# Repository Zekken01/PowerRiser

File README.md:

# PowerRiser – Lenovo Tiny 5 PCIe x8 + M.2 NVMe Riser (fork)

A passive riser for Lenovo Tiny 5 series PCs. It breaks the proprietary Lenovo riser connector out to an x8 PCIe slot and adds a 4-lane M.2 NVMe slot (2230/2242).

This is a modified fork of [nandfarm/PowerRiser](https://github.com/nandfarm/PowerRiser), which was inspired by [TinyRiser](https://github.com/a-little-wifi/Tinyriser) by WifiCable. See [Changes from upstream](#changes-from-upstream).

> ⚠ The changes in this fork have not been tested on hardware yet.

## Compatibility

Lenovo Tiny 5 series (8th/9th gen):

- ThinkCentre M720q
- ThinkCentre M920q
- ThinkCentre M920x
- ThinkStation P330 Tiny

It replaces the Lenovo risers with FRU codes 01AJ940, 01AJ902 and 01AJ929, and adds the M.2 slot. The back silkscreen also lists NEC Mate MC-3, MC-4 and MC-5.

The only physical change to the PC is removing the front metal bracket that holds the Bluetooth antenna.

## Usage & limitations

- **PCIe slot:** x8, closed at both ends as assembled. An x16 card fits only after you cut one end off the slot; see [Opening the slot for x16 cards](#opening-the-slot-for-x16-cards). It then runs at x8.
- **x16 cards:** slide the `PCIe CARD` switch (SW1) to **x16** or the card is not detected. SW1 is a small slide switch on the front, between the M.2 slot and the PCIe slot. The x16 position ties the slot's presence-detect line to GND. Leave it on **x8** for x1/x4/x8 cards. An x16 card's extra edge sits right over the M.2 drive, so check the clearance before you power on; see [Opening the slot for x16 cards](#opening-the-slot-for-x16-cards).
- **M.2 slot:** PCIe NVMe only, 2230 or 2242. SATA M.2 drives are not supported. Both drive lengths have a soldered M3 standoff; see [M.2 standoffs](#m2-standoffs).

## Pinouts

**AUX1** (left unpopulated; fit a 1×6 2.54 mm header if you need it. Pin 1 is the square pad):

| Pin | 1 | 2 | 3 | 4 | 5 | 6 |
|---|---|---|---|---|---|---|
| Signal | +12V | GND | +3.3V | GND | SMBCLK | SMBDATA |

**Fan header** (3-pin, 2.54 mm, keyed for a standard PC fan): GND, +12V, not connected. There is no tachometer or PWM signal, so 4-pin fans run at full speed.

**SW1 PCIe CARD** (C&K PCM12SMTR slide switch):

| Position | Contacts | Effect |
|---|---|---|
| x16 | 1–2 | Slot forced detected (needed for x16 cards) |
| x8 | 2–3 | No effect; x1/x4/x8 cards detect themselves |

## Changes from upstream

Compared with nandfarm/PowerRiser:

- **M.2 reset and clock request fixed.** `PERST#` and `CLKREQ#` were wired one pin early (pins 48 and 50 instead of 50 and 52), leaving the SSD's `CLKREQ#` unconnected. This matches the M.2 spec and TinyRiser now. It is the likely cause of the ASPM / L1 substate problems in the drive reports below.
- **x16 detect switch added.** SW1 `PCIe CARD`, an x16/x8 slide switch described above. The upstream files had no way to force detection.
- **AUX header reordered** so +12V is no longer next to +3.3V.
- **R1–R3 removed.** They were bypassed by copper and had no effect.
- **M.2 standoffs fitted at assembly.** Both standoff holes are in the BOM and placement file. Their drill is reduced from 4.4 mm to 4.3 mm to match the standoff datasheet (4.22 +0.08 mm), and their pads now have solder paste. The chassis screw post (H_Mount1) gets a 4 mm M3 SMT standoff on the bottom side, with paste on its pad.
- **Fan header moved up 1 mm.** It overlapped the end of the PCIe slot by about 0.4 mm. Its 12V feed and labels moved with it. Its holes are now 1.0 mm, as the 2510 datasheet asks (0.9 +0.1 mm).
- **Footprints checked against the datasheets.** The M.2 socket pads now match Foxconn's recommended layout, the PCIe slot's post holes are 2.35 mm, and slot pin A24 has a smaller pad so it clears the key notch by 0.2 mm.
- **JLC assembly files.** Every fitted part has an LCSC part number, including the PCIe slot, so the BOM and placement file cover the whole board.
- **3D models added** for the parts that had none, so the board renders complete.

## Building

Design files are in [`PowerRiser/`](PowerRiser) (KiCad 9).

PCB order settings (JLCPCB):

| Setting | Value |
|---|---|
| Layers | 4 |
| Thickness | 1.6 mm |
| Stackup | JLC04161H-3313, impedance control |
| Surface finish | ENIG |
| Gold fingers | Yes, 45° bevel |
| Copper | 1 oz outer, 0.5 oz inner |
| Vias | Tented |

Key parts:

| Part | MPN | LCSC |
|---|---|---|
| M.2 M-key socket (U1) | Foxconn AS0BC21-S30BM-7H | C2832351 |
| PCIe x8 slot, 98-pin (J1), closed end | UMAX 3183-10202P1T | C404115 |
| Fan header | 2510-3AW | C22451143 |
| x16/x8 slide switch (SW1) | C&K PCM12SMTR | C221841 |
| M.2 standoffs (H2230, H2242) | YIYUAN SMTSOM315BTR | C5221844 |
| Chassis screw post (H_Mount1, bottom side), M3 × 4 mm | YIYUAN SMTSOM340BTR | C5301786 |

For JLC assembly, the BOM and placement file cover every fitted part: J1, U1, the fan header, SW1, both M.2 standoffs, the chassis screw post, and the capacitors, resistors and LED. Choose standard PCBA with assembly on both sides, plus through-hole assembly for J1 and the fan header. AUX1 is left empty. Check the part rotations in JLC's placement preview before you confirm the order.

### Opening the slot for x16 cards

J1 is closed at both ends because no open-ended x8 slot that fits this footprint was in stock at JLC or LCSC when this was written. An x16 card needs one end of the slot cut off. The card then runs at x8.

1. Take the riser out of the PC and remove the M.2 drive.
2. Find the end of the slot furthest from the key. It is the end nearest SW1 and the M.2 slot. The x16 card's extra gold fingers come out here.
3. Cut straight down across the slot, from the top of the housing to the board, just past the last contact pair. Use a rotary tool (a Dremel or similar) with a thin cutting disc, or a fine hobby saw. The end block comes off in one piece. Keep the blade off the board surface.
4. Blow or brush the plastic dust out of the slot.
5. Slide SW1 to **x16**. Without this, the card is not detected.
6. Fit the M.2 drive, then the card, and check the clearance between them. The card's extra edge passes about 4 mm above the board, directly over the drive: over roughly the last 15 mm of a 2242 drive, or the last 4 mm of a 2230. Make sure the edge does not touch the drive, its parts or its label. An M.2 heatsink will not fit under the card.

Cut across the slot, not along the card channel. Cutting along the channel looks neater, but the disc is wide enough to damage the contacts. A cross cut removes more plastic and needs no precision.

*A good cut, shown on an x1 slot: cut along the lateral axis, across the slot. Photo by Marc Bevand, from [Tip to Use a Dremel to Cut Open a PCIe x1 Slot](https://blog.zorinaq.com/tip-to-use-a-dremel-to-cut-open-a-pcie-x1-slot/) (2011).*

### M.2 standoffs

JLC solders an SMTSOM315BTR standoff in both the 2230 and 2242 holes. It is an M3 surface-mount standoff, 1.5 mm tall, which matches the height of a drive in the M.2 socket.

- Fix the drive with an M3 × 3 mm pan-head screw in the standoff that matches its length. A 4 mm screw pokes slightly out of the bottom of the board.
- A 2242 drive passes over the 2230 standoff and touches it. The standoff is connected to GND. Check the underside of the drive at that point: if it has parts or bare pads there, put Kapton tape on top of the 2230 standoff. A drive with parts there may not sit flat.

## Drive reports (original nandfarm boards)

Collected by nandfarm from buyers of the original boards, before the M.2 fix above.

Reported OK:

- Crucial P310 2230 1TB
- Sabrent Rocket 2230 1TB (SB-2130-1TB)
- Kingston NV3 2230 (SNV3SM3/1T0)
- WD Black SN770M 2TB 2230
- Corsair MP600 Micro 2TB
- Intel DC P3605 1.6TB
- Micron 2400 Series MTFDKBK256TGE 256GB
- ADATA Legend 710 256GB
- Intel Optane M10 MEMPEK1J016GAH 16GB

Reported issues:

- SK Hynix PVC10 2230 1TB: not detected.
- SK Hynix BC711 2230 512GB: works only with ASPM off in the BIOS, or with the L1.1/L1.2 substates disabled in the OS.
- Micron 2400 Series MTFDKCD1T0QFM 1TB: detected at Windows startup, then disappears.

## License

CERN Open Hardware Licence v2 – Strongly Reciprocal ([CERN-OHL-S-2.0](LICENSE)).

This is a modified version of nandfarm/PowerRiser. The modifications are listed in [Changes from upstream](#changes-from-upstream) and were made in November 2026. Derived works must use the same licence. If you give or sell boards, tell recipients where the source is (this repository).

## Disclaimer

Use at your own risk. This design is provided for educational, experimental and hobbyist use, with no warranty. Check compatibility, power requirements and mechanical fit before installing.

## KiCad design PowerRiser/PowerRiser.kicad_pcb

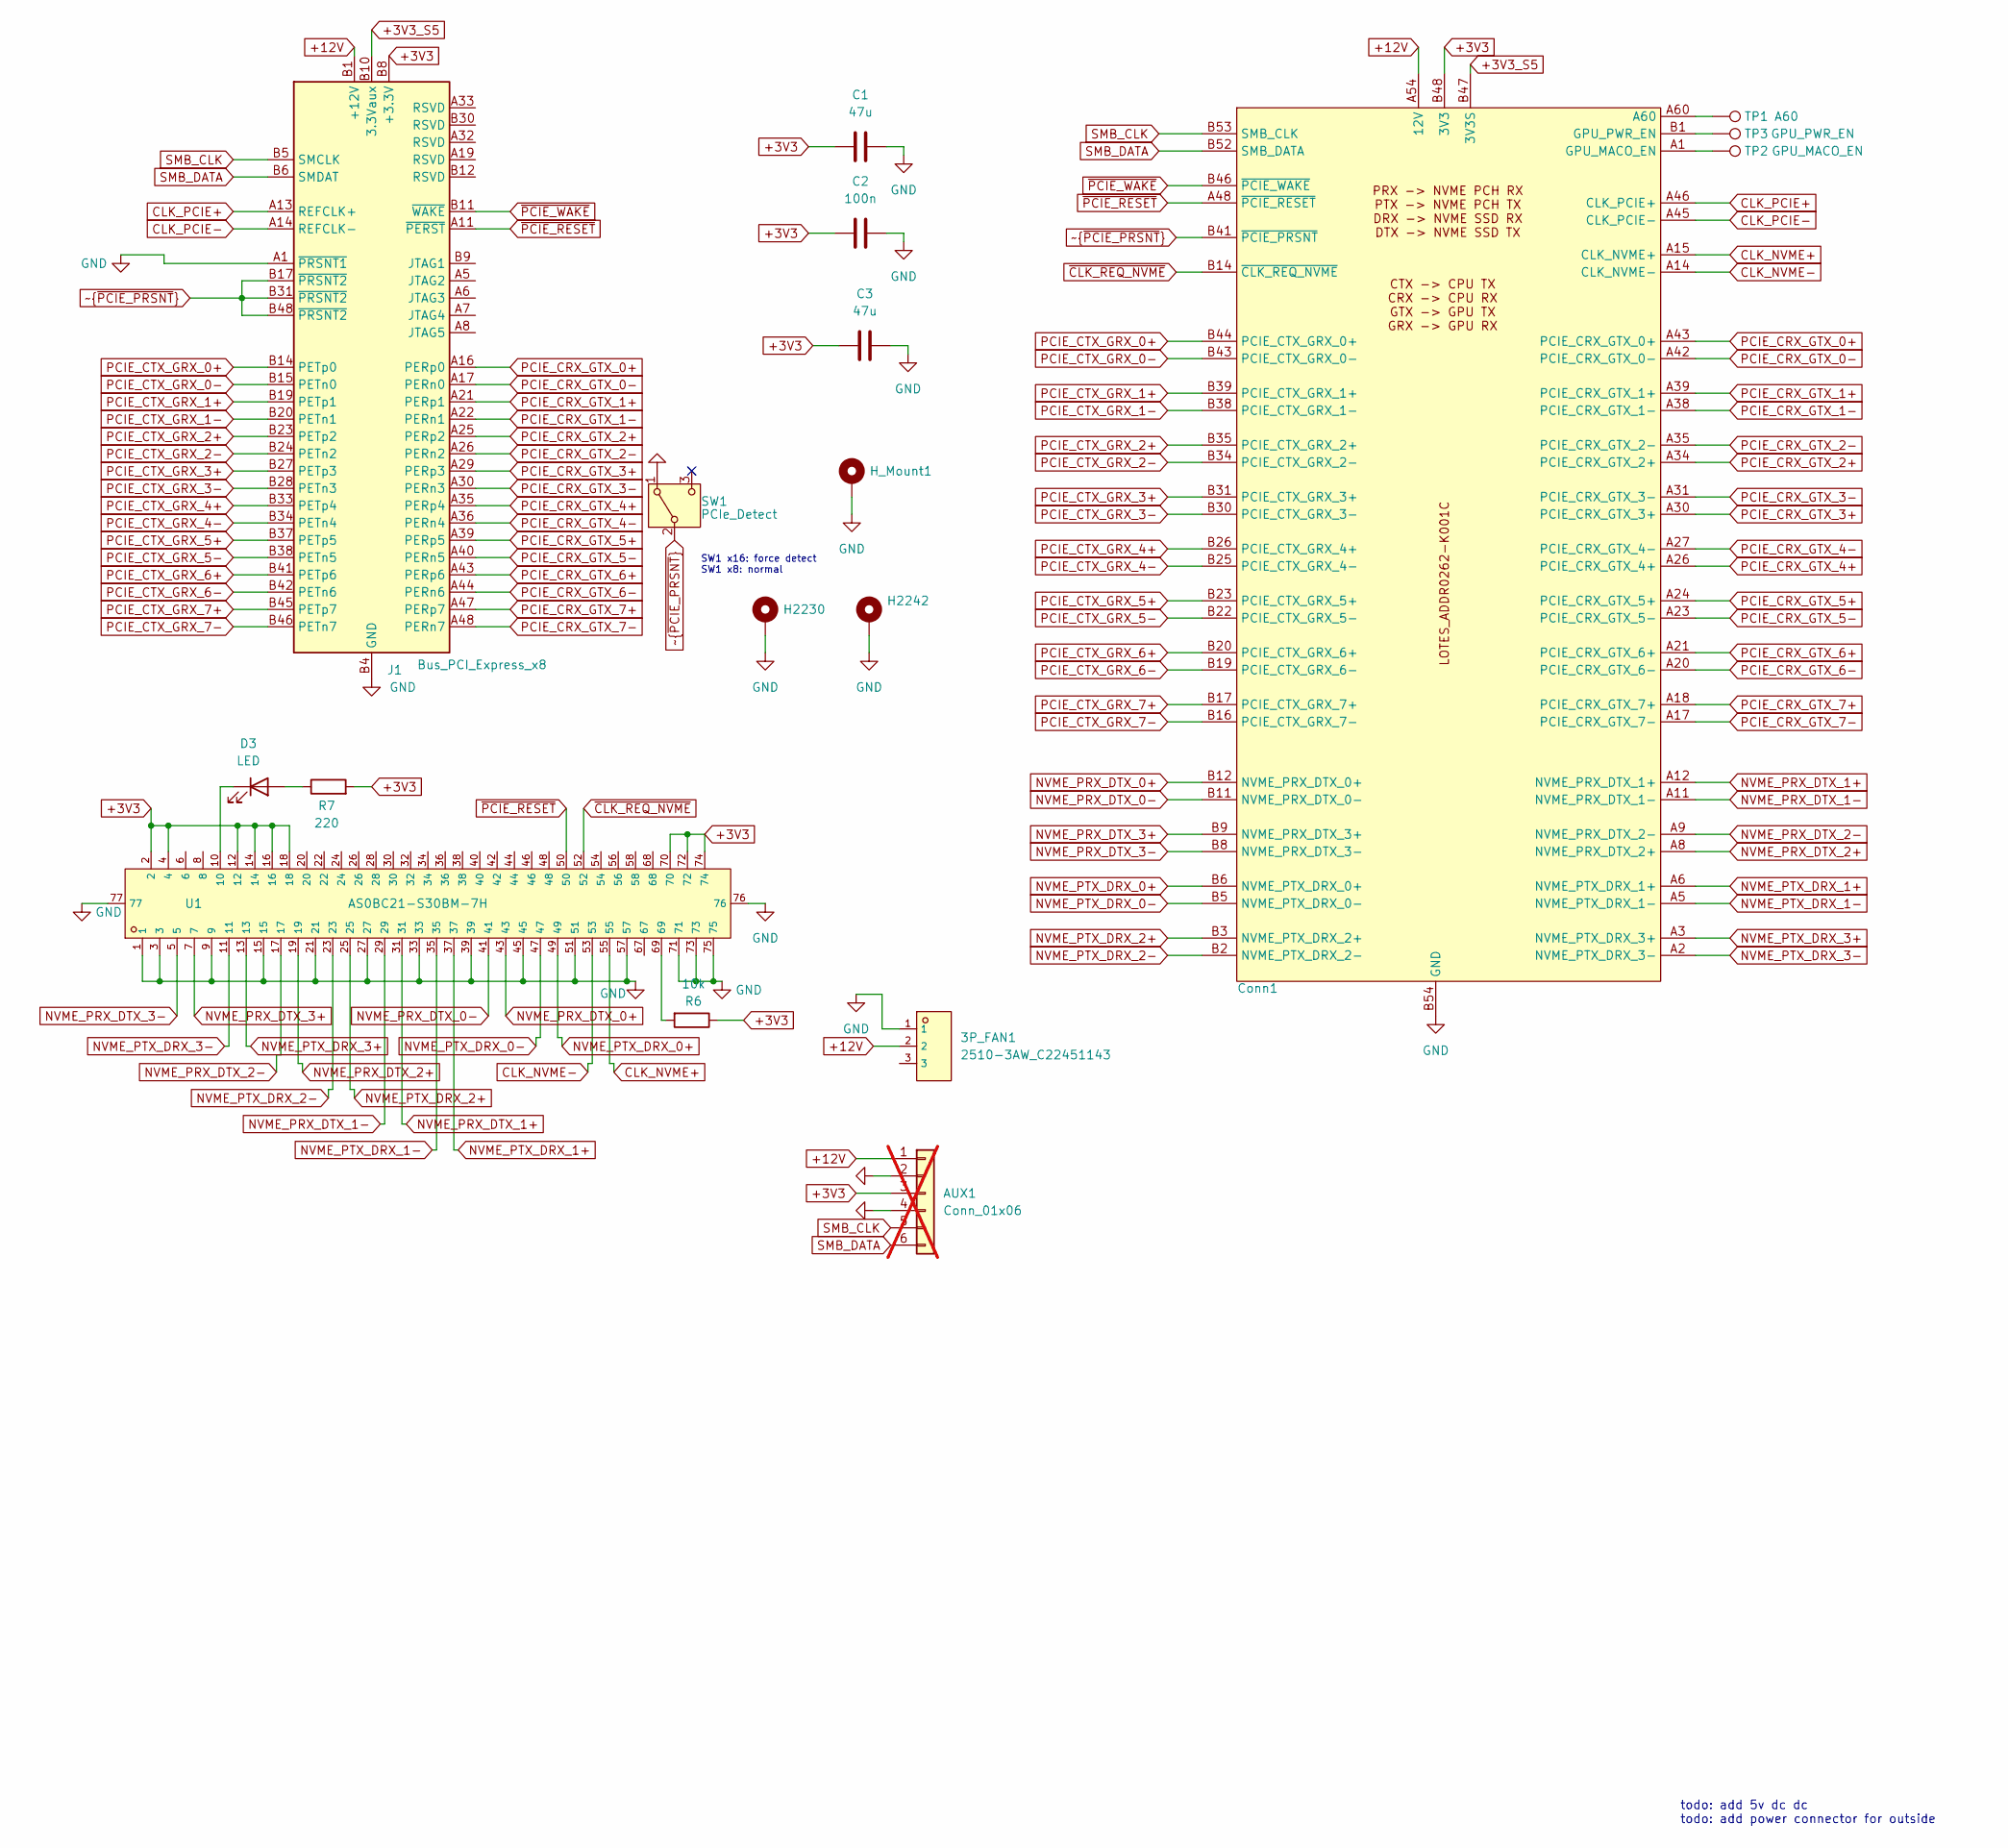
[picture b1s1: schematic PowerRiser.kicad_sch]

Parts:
3P_FAN1: 2510-3AW_C22451143; CONN-TH_2510-3AW; LCSC C22451143
AUX1: Conn_01x06; PinHeader_1x06_P2.54mm_Vertical; not fitted
C1, C3: 47u; C_1206_3216Metric_Pad1.33x1.80mm_HandSolder; LCSC C96123
C2: 100n; C_0805_2012Metric_Pad1.18x1.45mm_HandSolder; LCSC C49678
Conn1: Mx20qx_PCIe_FP
D3: LED; LED_0805_2012Metric; LCSC C2297
H2230, H2242: SMTSOM315BTR; MountingHole_4.3mm_M4_ISO7380_Pad_TopOnly; LCSC C5221844
H_Mount1: SMTSOM340BTR; MountingHole_4.3mm_M4_ISO7380_Pad_TopOnly; LCSC C5301786
J1: Bus_PCI_Express_x8; CONN-TH_98P-P1.00-V_3183-XXXXXPXT; LCSC C404115
R6: 10k; R_0805_2012Metric; LCSC C17414
R7: 220; R_0805_2012Metric; LCSC C17557
SW1: PCIe_Detect; SW_SPDT_PCM12; LCSC C221841
TP1: A60; TestPoint_Pad_D1.0mm
TP2: GPU_MACO_EN; TestPoint_Pad_D1.0mm
TP3: GPU_PWR_EN; TestPoint_Pad_D1.0mm
U1: AS0BC21-S30BM-7H; CONN-SMD_AS0BC21-S30BM-7H; LCSC C2832351

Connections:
+3V3: AUX1.3, C1.1, C2.1, C3.1, Conn1.A51 (3V3), Conn1.A52 (3V3), Conn1.A53 (3V3), Conn1.B48 (3V3), Conn1.B49 (3V3), Conn1.B50 (3V3), J1.A9 (+3.3V), J1.A10 (+3.3V), J1.B8 (+3.3V), R6.1, R7.2, U1.2, U1.4, U1.12, U1.14, U1.16, U1.18, U1.70, U1.72, U1.74
+3V3_S5: Conn1.A50 (3V3S), Conn1.B47 (3V3S), J1.B10 (3.3Vaux)
+12V: 3P_FAN1.2, AUX1.1, Conn1.A54 (12V), Conn1.A55 (12V), Conn1.A56 (12V), Conn1.A57 (12V), Conn1.A58 (12V), Conn1.A59 (12V), Conn1.B55 (12V), Conn1.B56 (12V), Conn1.B57 (12V), Conn1.B58 (12V), Conn1.B59 (12V), Conn1.B60 (12V), J1.A2 (+12V), J1.A3 (+12V), J1.B1 (+12V), J1.B2 (+12V), J1.B3 (+12V)
CLK_NVME+: Conn1.A15 (CLK_NVME+), U1.55
CLK_NVME-: Conn1.A14 (CLK_NVME-), U1.53
CLK_PCIE+: Conn1.A46 (CLK_PCIE+), J1.A13 (REFCLK+)
CLK_PCIE-: Conn1.A45 (CLK_PCIE-), J1.A14 (REFCLK-)
GND: 3P_FAN1.1, AUX1.2, AUX1.4, C1.2, C2.2, C3.2, Conn1.A4 (GND), Conn1.A7 (GND), Conn1.A10 (GND), Conn1.A13 (GND), Conn1.A16 (GND), Conn1.A19 (GND), Conn1.A22 (GND), Conn1.A25 (GND), Conn1.A28 (GND), Conn1.A29 (GND), Conn1.A32 (GND), Conn1.A33 (GND), Conn1.A36 (GND), Conn1.A37 (GND), Conn1.A40 (GND), Conn1.A41 (GND), Conn1.A44 (GND), Conn1.A47 (GND), Conn1.A49 (GND), Conn1.B4 (GND), Conn1.B7 (GND), Conn1.B10 (GND), Conn1.B13 (GND), Conn1.B15 (GND), Conn1.B18 (GND), Conn1.B21 (GND), Conn1.B24 (GND), Conn1.B27 (GND), Conn1.B29 (GND), Conn1.B32 (GND), Conn1.B33 (GND), Conn1.B36 (GND), Conn1.B37 (GND), Conn1.B40 (GND), Conn1.B42 (GND), Conn1.B45 (GND), Conn1.B51 (GND), Conn1.B54 (GND), H2230.1, H2242.1, H_Mount1.1, J1.A1 (~PRSNT1), J1.A4 (GND), J1.A12 (GND), J1.A15 (GND), J1.A18 (GND), J1.A20 (GND), J1.A23 (GND), J1.A24 (GND), J1.A27 (GND), J1.A28 (GND), J1.A31 (GND), J1.A34 (GND), J1.A37 (GND), J1.A38 (GND), J1.A41 (GND), J1.A42 (GND), J1.A45 (GND), J1.A46 (GND), J1.A49 (GND), J1.B4 (GND), J1.B7 (GND), J1.B13 (GND), J1.B16 (GND), J1.B18 (GND), J1.B21 (GND), J1.B22 (GND), J1.B25 (GND), J1.B26 (GND), J1.B29 (GND), J1.B32 (GND), J1.B35 (GND), J1.B36 (GND), J1.B39 (GND), J1.B40 (GND), J1.B43 (GND), J1.B44 (GND), J1.B47 (GND), J1.B49 (GND), SW1.1 (A), U1.1, U1.3, U1.9, U1.15, U1.21, U1.27, U1.33, U1.39, U1.45, U1.51, U1.57, U1.71, U1.73, U1.75, U1.76, U1.77
NVME_PRX_DTX_0+: Conn1.B12 (NVME_PRX_DTX_0+), U1.43
NVME_PRX_DTX_0-: Conn1.B11 (NVME_PRX_DTX_0-), U1.41
NVME_PRX_DTX_1+: Conn1.A12 (NVME_PRX_DTX_1+), U1.31
NVME_PRX_DTX_1-: Conn1.A11 (NVME_PRX_DTX_1-), U1.29
NVME_PRX_DTX_2+: Conn1.A8 (NVME_PRX_DTX_2+), U1.19
NVME_PRX_DTX_2-: Conn1.A9 (NVME_PRX_DTX_2-), U1.17
NVME_PRX_DTX_3+: Conn1.B9 (NVME_PRX_DTX_3+), U1.7
NVME_PRX_DTX_3-: Conn1.B8 (NVME_PRX_DTX_3-), U1.5
NVME_PTX_DRX_0+: Conn1.B6 (NVME_PTX_DRX_0+), U1.49
NVME_PTX_DRX_0-: Conn1.B5 (NVME_PTX_DRX_0-), U1.47
NVME_PTX_DRX_1+: Conn1.A6 (NVME_PTX_DRX_1+), U1.37
NVME_PTX_DRX_1-: Conn1.A5 (NVME_PTX_DRX_1-), U1.35
NVME_PTX_DRX_2+: Conn1.B3 (NVME_PTX_DRX_2+), U1.25
NVME_PTX_DRX_2-: Conn1.B2 (NVME_PTX_DRX_2-), U1.23
NVME_PTX_DRX_3+: Conn1.A3 (NVME_PTX_DRX_3+), U1.13
NVME_PTX_DRX_3-: Conn1.A2 (NVME_PTX_DRX_3-), U1.11
unnamed: Conn1.A1 (GPU_MACO_EN), TP2.1
unnamed: Conn1.B1 (GPU_PWR_EN), TP3.1
unnamed: Conn1.A60, TP1.1
unnamed: D3.2 (A), R7.1
unnamed: D3.1 (K), U1.10
unnamed: R6.2, U1.69
PCIE_CRX_GTX_0+: Conn1.A43 (PCIE_CRX_GTX_0+), J1.A16 (PERp0)
PCIE_CRX_GTX_0-: Conn1.A42 (PCIE_CRX_GTX_0-), J1.A17 (PERn0)
PCIE_CRX_GTX_1+: Conn1.A39 (PCIE_CRX_GTX_1+), J1.A21 (PERp1)
PCIE_CRX_GTX_1-: Conn1.A38 (PCIE_CRX_GTX_1-), J1.A22 (PERn1)
PCIE_CRX_GTX_2+: Conn1.A34 (PCIE_CRX_GTX_2+), J1.A25 (PERp2)
PCIE_CRX_GTX_2-: Conn1.A35 (PCIE_CRX_GTX_2-), J1.A26 (PERn2)
PCIE_CRX_GTX_3+: Conn1.A30 (PCIE_CRX_GTX_3+), J1.A29 (PERp3)
PCIE_CRX_GTX_3-: Conn1.A31 (PCIE_CRX_GTX_3-), J1.A30 (PERn3)
PCIE_CRX_GTX_4+: Conn1.A26 (PCIE_CRX_GTX_4+), J1.A35 (PERp4)
PCIE_CRX_GTX_4-: Conn1.A27 (PCIE_CRX_GTX_4-), J1.A36 (PERn4)
PCIE_CRX_GTX_5+: Conn1.A24 (PCIE_CRX_GTX_5+), J1.A39 (PERp5)
PCIE_CRX_GTX_5-: Conn1.A23 (PCIE_CRX_GTX_5-), J1.A40 (PERn5)
PCIE_CRX_GTX_6+: Conn1.A21 (PCIE_CRX_GTX_6+), J1.A43 (PERp6)
PCIE_CRX_GTX_6-: Conn1.A20 (PCIE_CRX_GTX_6-), J1.A44 (PERn6)
PCIE_CRX_GTX_7+: Conn1.A18 (PCIE_CRX_GTX_7+), J1.A47 (PERp7)
PCIE_CRX_GTX_7-: Conn1.A17 (PCIE_CRX_GTX_7-), J1.A48 (PERn7)
PCIE_CTX_GRX_0+: Conn1.B44 (PCIE_CTX_GRX_0+), J1.B14 (PETp0)
PCIE_CTX_GRX_0-: Conn1.B43 (PCIE_CTX_GRX_0-), J1.B15 (PETn0)
PCIE_CTX_GRX_1+: Conn1.B39 (PCIE_CTX_GRX_1+), J1.B19 (PETp1)
PCIE_CTX_GRX_1-: Conn1.B38 (PCIE_CTX_GRX_1-), J1.B20 (PETn1)
PCIE_CTX_GRX_2+: Conn1.B35 (PCIE_CTX_GRX_2+), J1.B23 (PETp2)
PCIE_CTX_GRX_2-: Conn1.B34 (PCIE_CTX_GRX_2-), J1.B24 (PETn2)
PCIE_CTX_GRX_3+: Conn1.B31 (PCIE_CTX_GRX_3+), J1.B27 (PETp3)
PCIE_CTX_GRX_3-: Conn1.B30 (PCIE_CTX_GRX_3-), J1.B28 (PETn3)
PCIE_CTX_GRX_4+: Conn1.B26 (PCIE_CTX_GRX_4+), J1.B33 (PETp4)
PCIE_CTX_GRX_4-: Conn1.B25 (PCIE_CTX_GRX_4-), J1.B34 (PETn4)
PCIE_CTX_GRX_5+: Conn1.B23 (PCIE_CTX_GRX_5+), J1.B37 (PETp5)
PCIE_CTX_GRX_5-: Conn1.B22 (PCIE_CTX_GRX_5-), J1.B38 (PETn5)
PCIE_CTX_GRX_6+: Conn1.B20 (PCIE_CTX_GRX_6+), J1.B41 (PETp6)
PCIE_CTX_GRX_6-: Conn1.B19 (PCIE_CTX_GRX_6-), J1.B42 (PETn6)
PCIE_CTX_GRX_7+: Conn1.B17 (PCIE_CTX_GRX_7+), J1.B45 (PETp7)
PCIE_CTX_GRX_7-: Conn1.B16 (PCIE_CTX_GRX_7-), J1.B46 (PETn7)
SMB_CLK: AUX1.5, Conn1.B53 (SMB_CLK), J1.B5 (SMCLK)
SMB_DATA: AUX1.6, Conn1.B52 (SMB_DATA), J1.B6 (SMDAT)
~CLK_REQ_NVME: Conn1.B14 (~CLK_REQ_NVME), U1.52
~PCIE_RESET: Conn1.A48 (~PCIE_RESET), J1.A11 (~PERST), U1.50
~PCIE_WAKE: Conn1.B46 (~PCIE_WAKE), J1.B11 (~WAKE)
~~{PCIE_PRSNT}: Conn1.B28 (~PCIE_PRSNT), Conn1.B41 (~PCIE_PRSNT), J1.B17 (~PRSNT2), J1.B31 (~PRSNT2), J1.B48 (~PRSNT2), SW1.2 (B)

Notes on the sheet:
todo: add 5v dc dc todo: add power connector for outside
SW1 x16: force detect SW1 x8: normal

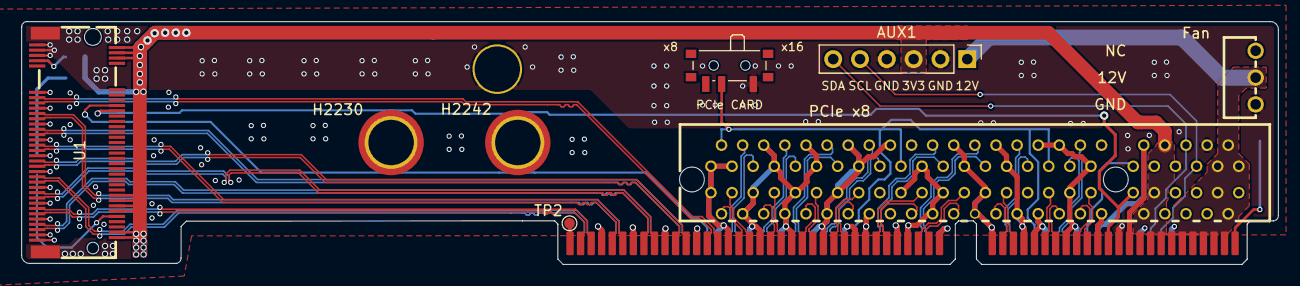
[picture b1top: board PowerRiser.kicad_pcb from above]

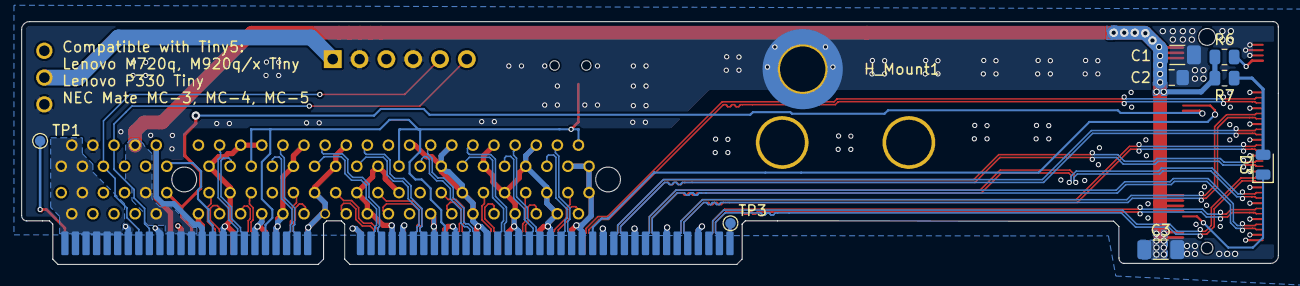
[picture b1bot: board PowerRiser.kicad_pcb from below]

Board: 4 copper layers, 119.0 x 23.0 mm, 18 parts (9 on the bottom side), 68 nets.
